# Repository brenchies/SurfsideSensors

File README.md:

# Project scope
The idea behind this project was to create a sensor module that is easy to replicate and upgraded.
The easiest way to achieve this was to have an object oriented approach, in which everything from the sesnors to the communiction devices are defined as an object.
This meant that we had deal with generic types and in case of some cases even variadic generic types, which a combination that you don't generally come accross.
To solve this, templates and ellipses were used, during the creation of the surfsidescience class which is the class that handles the generic types.

We wanted this project to not be bount to a specific microcontroller so we prevented making MCU specific code part of the surfsidescience class. But instead when needed MCU specif code was written in the main file that is easilly accessible.
MCU specifc classes that are used are the sleep function and the watchdog timer that are specific to the ESP32. This project was based on the LilyGO-T-SIM7000G, for more information about this board please consult their github repo: https://github.com/Xinyuan-LilyGO/LilyGO-T-SIM7000G.

## The surfsidescience class has three main methods

template typename... sensorType <br>
void processSensors(sensorType&... sensors)<br>
This method handles the sensors in the followwing way:
- turn sensors on
- read the sensors
- turn off the sensors
- collect errors from the sensors

template typename modemType
int postData(modemType Modem, bool reportRSSI=true) 
This method handles the modem in the following way:
- turn on modem
- establish internet connection
- get network time
- post data
- disable modem
- collect errors from modem

template typename loggerType<br>
int log(loggerType logger)<br>
This method handles the logger in the following way:
- write data to temporary file if data was not uploaded
- write data to data file
- write error to error file

# Writing a sensor class
Writing a class can be done by using the inheriting the sensorBase class and overwriting the virtual functions:
- int enableSensorsImpl(int *sensorstatus)
- int disableSensorsImpl(int *sensorstatus)
- int calibrateSensorsImpl(int statusLed, int *sensorstatus)
- int readSensorImpl(float *buffer, int *sensorstatus, long delay_)

Furthermore the follwing variables have to be modified accroding to the users needs
- int ENABLEPIN;
- int averagingSamples;
- bool checkValueInRange;
- unsinged long sensorPwrDelay;
- unsinged long sampleReadDelay;
- bool SENSOR_ENABLE_STATE;
- String sensorName[i];
- String units[i];
- int numberOfreadings;
- unsinged long sensorStabilizeDelay[i];
- int sensorReadingDecimals[i];
- float EXPECTED_VALUE_MIN[i]=low;
- float EXPECTED_VALUE_MAX[i]=max;

# Dependencies 
- robtillaart/SHT31@^0.3.6
- vshymanskyy/TinyGSM@^0.11.5
- arduino-libraries/ArduinoHttpClient@^0.4.0
- mulmer89/EZO I2C Sensors@1.0.0+32e1eda
- vshymanskyy/StreamDebugger@^1.0.1
- plerup/EspSoftwareSerial@^6.16.1
- fu-hsi/PMS Library@^1.1.0

# TODO
- standerdize the modem class to a more generic type, since this is currently not structured in a user friendly way
- make a serverHandler method for the surfsidescience class, which will allow more flexibility for server specific accions
- Server class needs to be introduced with at least endpoint for error reporting, datareport, and updates checking endpoint.
- Standerdize logger class 
- have more controll over sleep times, since sleep is just set to certain amount of seconds which means that the sample upload time will drift over time.
- find a way to introduce a more reliable time source since the time is network dependent so when the network is unreachable, there will be no timestamp with the stored temporary data
- the TinyGSM library is being, during the posting process if the server cannot be reached, the loop will hang there forever, currently this bug is pached with the use of a watchdog timer that has a timout of 10 minutes.
- Simplify the amount of variables of the sesnorBase class. Currently a lot is done for the user in exchange at the cost of them requirening so many input variables to the sesnorBase class.

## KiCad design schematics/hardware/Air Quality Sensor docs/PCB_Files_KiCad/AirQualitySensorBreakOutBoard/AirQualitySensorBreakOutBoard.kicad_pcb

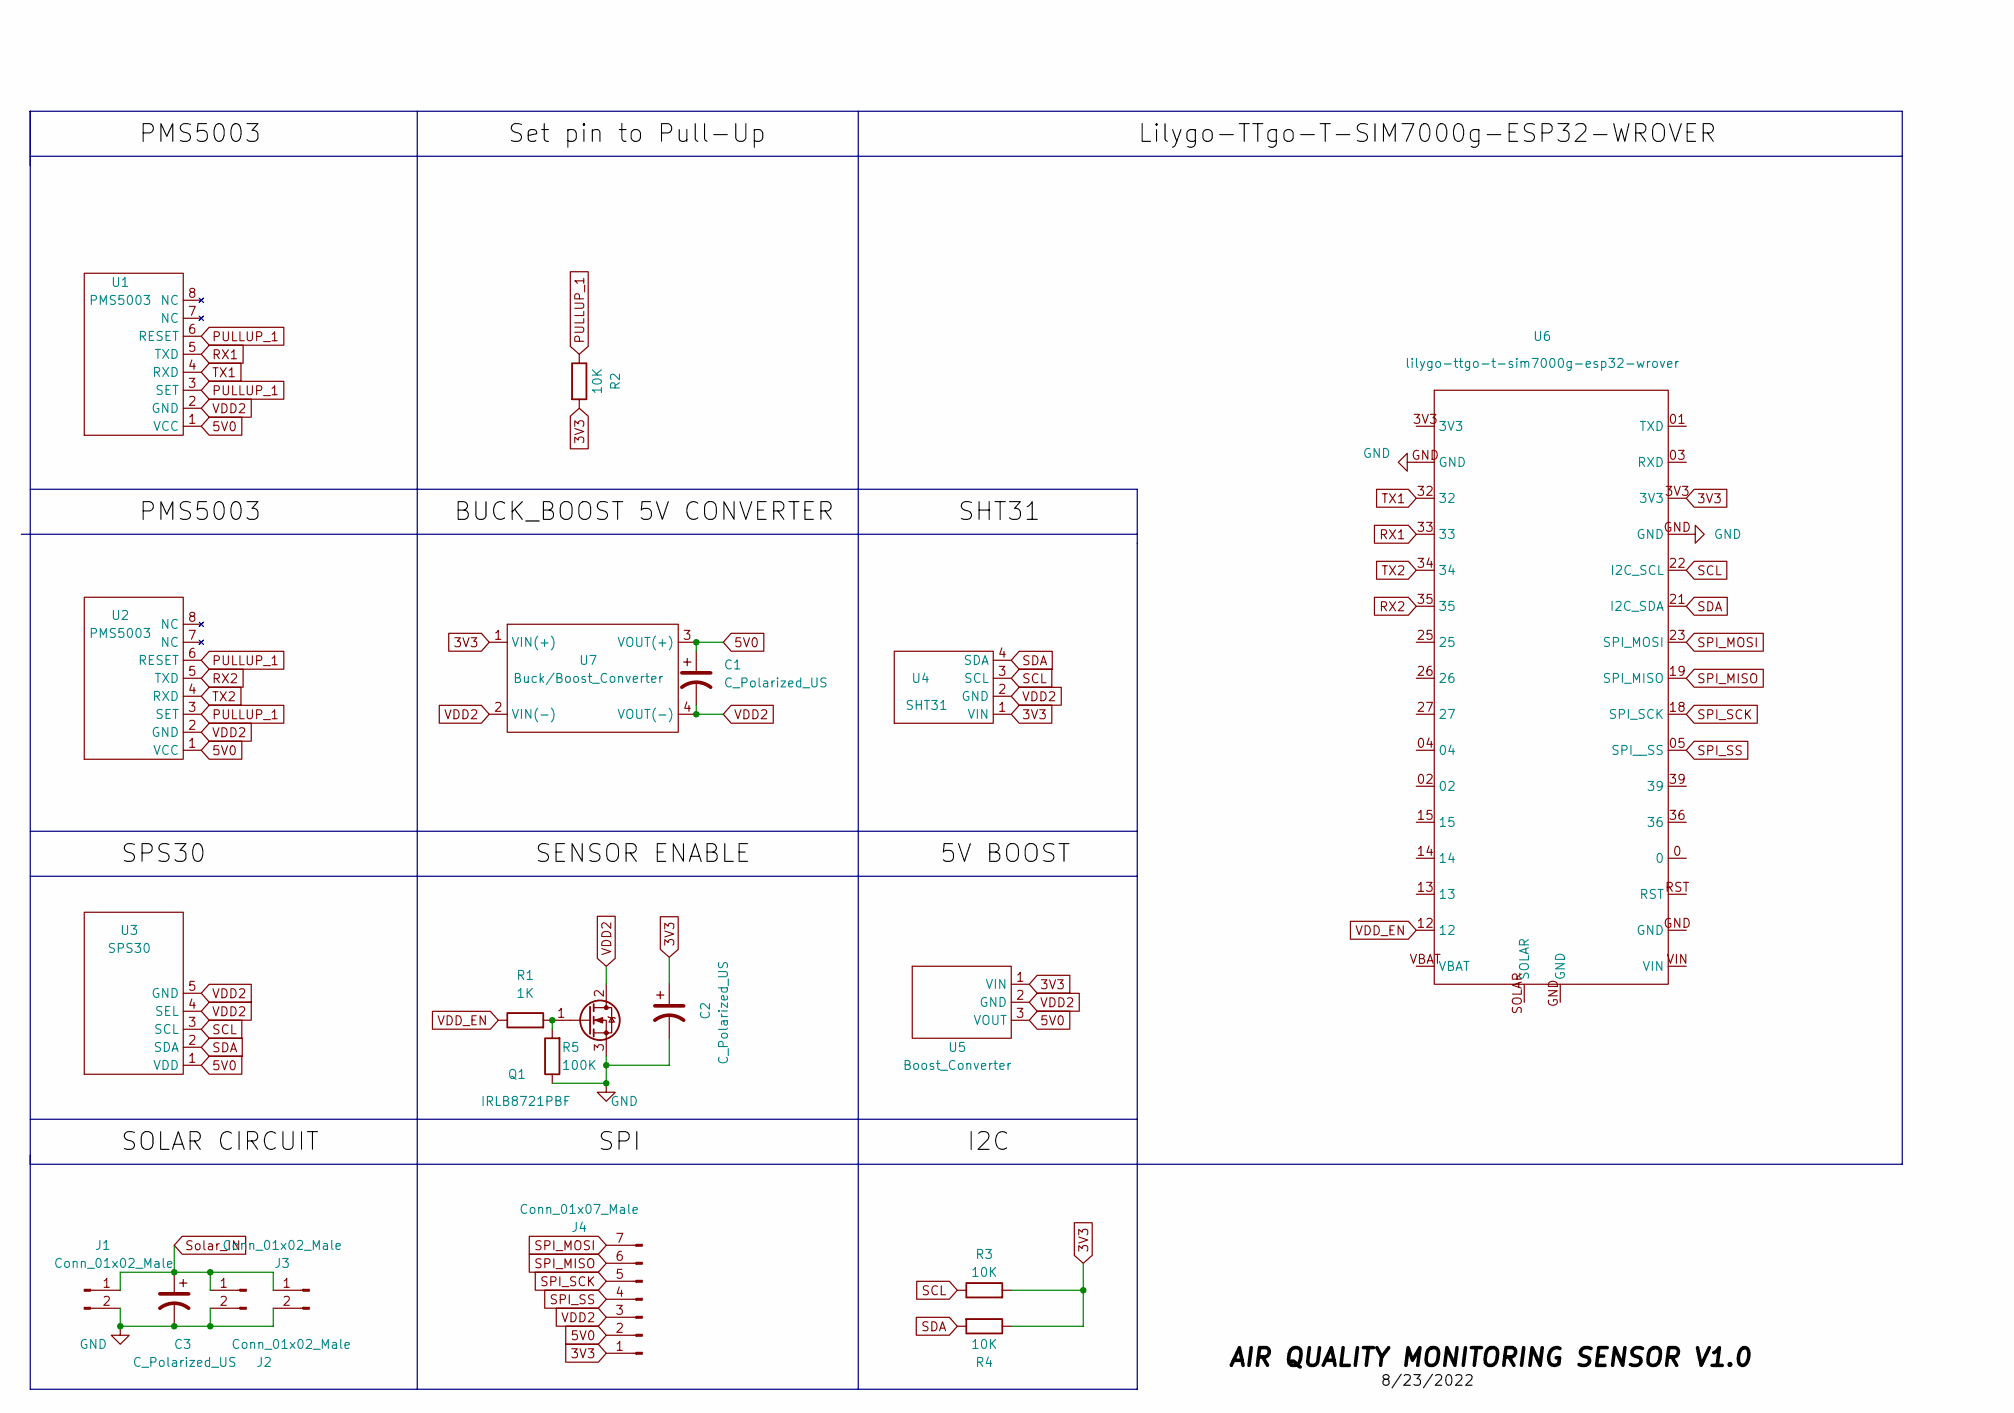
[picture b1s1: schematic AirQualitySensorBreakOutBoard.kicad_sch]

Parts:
C1, C2, C3: C_Polarized_US; CP_Radial_D6.3mm_P2.50mm
J1, J2, J3: Conn_01x02_Male; JST_XH_B2B-XH-AM_1x02_P2.50mm_Vertical
J4: Conn_01x07_Male; PinHeader_1x07_P2.54mm_Vertical
Q1: IRLB8721PBF; TO-220-3_Vertical
R1: 1K; R_Axial_DIN0204_L3.6mm_D1.6mm_P7.62mm_Horizontal
R2, R3, R4: 10K; R_Axial_DIN0204_L3.6mm_D1.6mm_P7.62mm_Horizontal
R5: 100K; R_Axial_DIN0204_L3.6mm_D1.6mm_P7.62mm_Horizontal
U1, U2: PMS5003
U3: SPS30
U4: SHT31
U5: Boost_Converter
U6: lilygo-ttgo-t-sim7000g-esp32-wrover; ilygo-ttgo-t-sim7000g-esp32-wrover
U7: Buck/Boost_Converter; Buck_Boost_Converter

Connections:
3V3: C2.1, J4.1, R2.2, R3.2, R4.1, U4.1 (VIN), U5.1 (VIN), U6.3V3, U7.1 (VIN(+))
5V0: C1.1, J4.2, U1.1 (VCC), U2.1 (VCC), U3.1 (VDD), U5.3 (VOUT), U7.3 (VOUT(+))
GND: C2.2, C3.2, J1.2, J2.2, J3.2, Q1.3 (S), R5.1, U6.GND
unnamed: Q1.1 (G), R1.2, R5.2
PULLUP_1: R2.1, U1.3 (SET), U1.6 (RESET), U2.3 (SET), U2.6 (RESET)
RX1: U1.5 (TXD), U6.33
RX2: U2.5 (TXD), U6.35
SCL: R3.1, U3.3 (SCL), U4.3 (SCL), U6.22 (I2C_SCL)
SDA: R4.2, U3.2 (SDA), U4.4 (SDA), U6.21 (I2C_SDA)
SPI_MISO: J4.6, U6.19 (SPI_MISO)
SPI_MOSI: J4.7, U6.23 (SPI_MOSI)
SPI_SCK: J4.5, U6.18 (SPI_SCK)
SPI_SS: J4.4, U6.05 (SPI__SS)
Solar_IN: C3.1, J1.1, J2.1, J3.1
TX1: U1.4 (RXD), U6.32
TX2: U2.4 (RXD), U6.34
VDD2: C1.2, J4.3, Q1.2 (D), U1.2 (GND), U2.2 (GND), U3.4 (SEL), U3.5 (GND), U4.2 (GND), U5.2 (GND), U7.2 (VIN(-)), U7.4 (VOUT(-))
VDD_EN: R1.1, U6.12

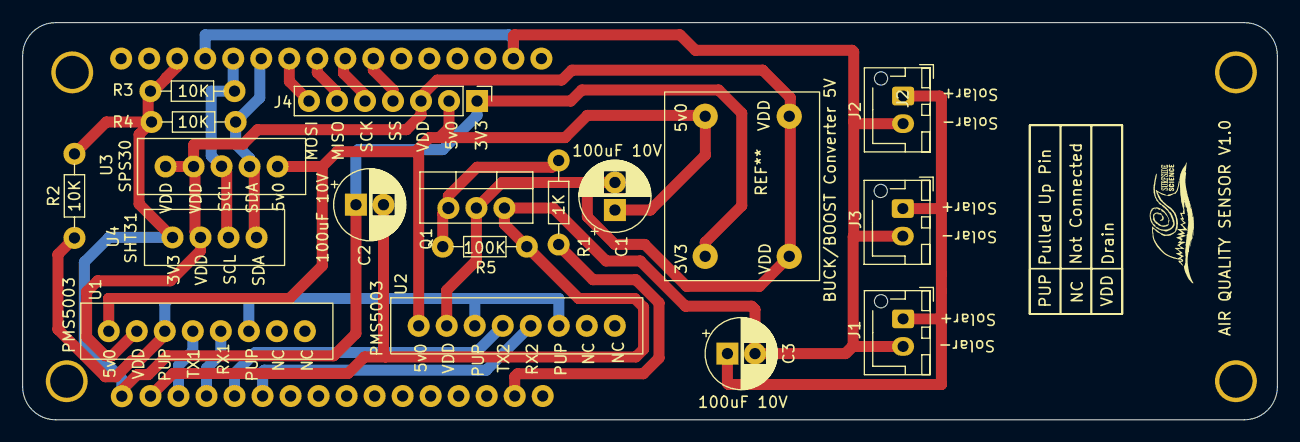
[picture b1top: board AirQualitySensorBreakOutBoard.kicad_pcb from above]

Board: 2 copper layers, 113.8 x 36.0 mm, 18 parts (0 on the bottom side), 18 nets.

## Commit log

2022-08-04 Initial Push
2022-08-04 Adding AQS PCB files in AQS directory
    (Air Quality Sensor)
2022-08-05 updated version
2022-08-06 PMS.h and PMS.cpp fixed
2022-08-08 WaterQuality project creation PIO
2022-08-08 VS_Code Demo
2022-08-08 Got my doc file back
2022-08-08 Added protocol design for PM Sensors
2022-08-08 surfscidescience library with template and stdarg
2022-08-08 GSM connectivity working
2022-08-08 Revert "cpp"
    This reverts commit 4e778a0979fc24f7705b3601a6d5554a9a853ffc.
2022-08-09 Communication success with Database
    Sensor values are not accurate though
2022-08-09 Draw io architecture
2022-08-09 sd card support & do library
2022-08-09 draw io change
2022-08-09 SHT31 dev
2022-08-09 stuck
2022-08-09 Fixed Sensor_Calibration_Period
    from 3s to 30s
2022-08-09 ezo_rtd_i2c updates
2022-08-09 Fixed!
    Can now Send Temp, Humidity and particulates to Database
2022-08-10 ezo_ec_i2c, ezo_ph_i2c, ezo_do_i2c, libraries added
2022-08-10 ezo_rtd_i2c debugged -> can be used as a template for other sensors classes
2022-08-10 integrating
2022-08-10 updated modem and sensors classes
    sensors library updated error report & modem class updated to have closed loop power enable and disable checks
2022-08-10 SHT31_LIB updating
2022-08-11 Update SHT31 lib
2022-08-11 sensor base class begin development from ezo_rtd_i2c class
2022-08-11 SHT31 BUG
    compiles and runs but theres a bug
2022-08-11 Still Bug
    fuck
2022-08-11 template class for sensors , there is a bug when the For the sensor implemnetation from the main library reverting to prev version for the niight
2022-08-12 Fixed SHT31 bug
    now protocol payload is implemented and sensor measures accurately
2022-08-12 Documenting SHT31LIB
2022-08-12 Added PMS
2022-08-12 Development process for PMS-Lib class
2022-08-12 aggg stupid head made me loose all my changes luckilly VSCODE had a backup of the sesnorBase class and voltageSesnorClass
    And previous bugs solutions are still known
2022-08-12 sensorBase and voltageSensor class stable
    stable version of sensor base and some sensor voltage sensor class was made from the sensorBase;
    recovery from stupid head detaching which resulted in deleted progress
2022-08-12 Testing virtual override
2022-08-12 Adding AQS files here
2022-08-12 SHT31_Lib implemented
2022-08-13 done for the weekend
    modme update class for rssi, surfscience class update sdcard error, add dataUploadstatus.
    surfscience.processSensors needs to be revised, supports only one two objects at a time
2022-08-13 Succesfully Integration and uploading measurements to database
    Add battery voltage and solar voltage, to be reported to database as well as the label of the SPS30,
    bug: PMS class supports only 1 instance -> SurfSideScience process crashes
2022-08-13 tinygsms.post return added
2022-08-15 Fixed bug aqs
2022-08-17 surfsice.processSensor multi argument fixed
    surfsice.processSensor ellipses fixed. function can now take multiple argument variadic classes
2022-08-17 ezo_ph_i2cc
    temperature compensation feature added
2022-08-18 calibration & compensation for ezo_xx_i2c
    support added but needs to be debugged
2022-08-18 Updated AQS sensor code
2022-08-19 Added esp_task_wdt function
    This function is for making sure the esp reconnects to the internet when there is interference with tinygsm
2022-08-19 field test upgrades
    timezone changed to +4 for time correction, added watchdog timer to ensure max process time is 10 minutes and prevent an endless loop.
    added return to the postData loop if successful posting. Enabled RSSI reporting
2022-08-22 draw IO classes update
2022-08-22 Updated AQS sensor code
    fixed multiple post bug and, tinyGSM not re-connecting bug
2022-08-22 Adding AQS files to this branch
2022-08-22 draw io update
2022-09-01 Main update
    Final deliverables
    Readme
    examples
    instructions
    schematics
2022-09-01 added ezo_xxx caliubration example
2022-09-01 Edited AQS example
2022-09-01 waterquality gerber added
2022-09-01 Added AQS docs
    Schematic, gerber files, pcb kicad files
2022-09-02 readme update
2022-09-07 Zipped PCB Files and Gerber Files of Air quality sensor
2022-09-07 Compressed fritzing file to zip
2022-10-12 fix error template for sensor enabling and disabling
2022-10-26 =set network mode to 13 (gsm only)
2022-11-30 Update airQuality.ino
    Changed device name to avoid accidental pollution of FAB data
2022-12-22 Update sdlogger.cpp
    wrong library was included
2022-12-22 Create AQoffline.ino
    version of air quality example to work without GSM connection while plugged in, for validation purposes. Data is logged to the SD card and sent to serial monitor.
2023-05-29 Create 3D prints
